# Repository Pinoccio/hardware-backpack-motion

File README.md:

motino-hardware-reference
===========================

Contained are the schematics, board layout, data sheets, and BOM for the Pinoccio motion shield, containing GPS, accelerometer, digital compass, and 3-axis gyro.

The board revisions are also marked as tags in the git repository, if you'd like to see a previous version.

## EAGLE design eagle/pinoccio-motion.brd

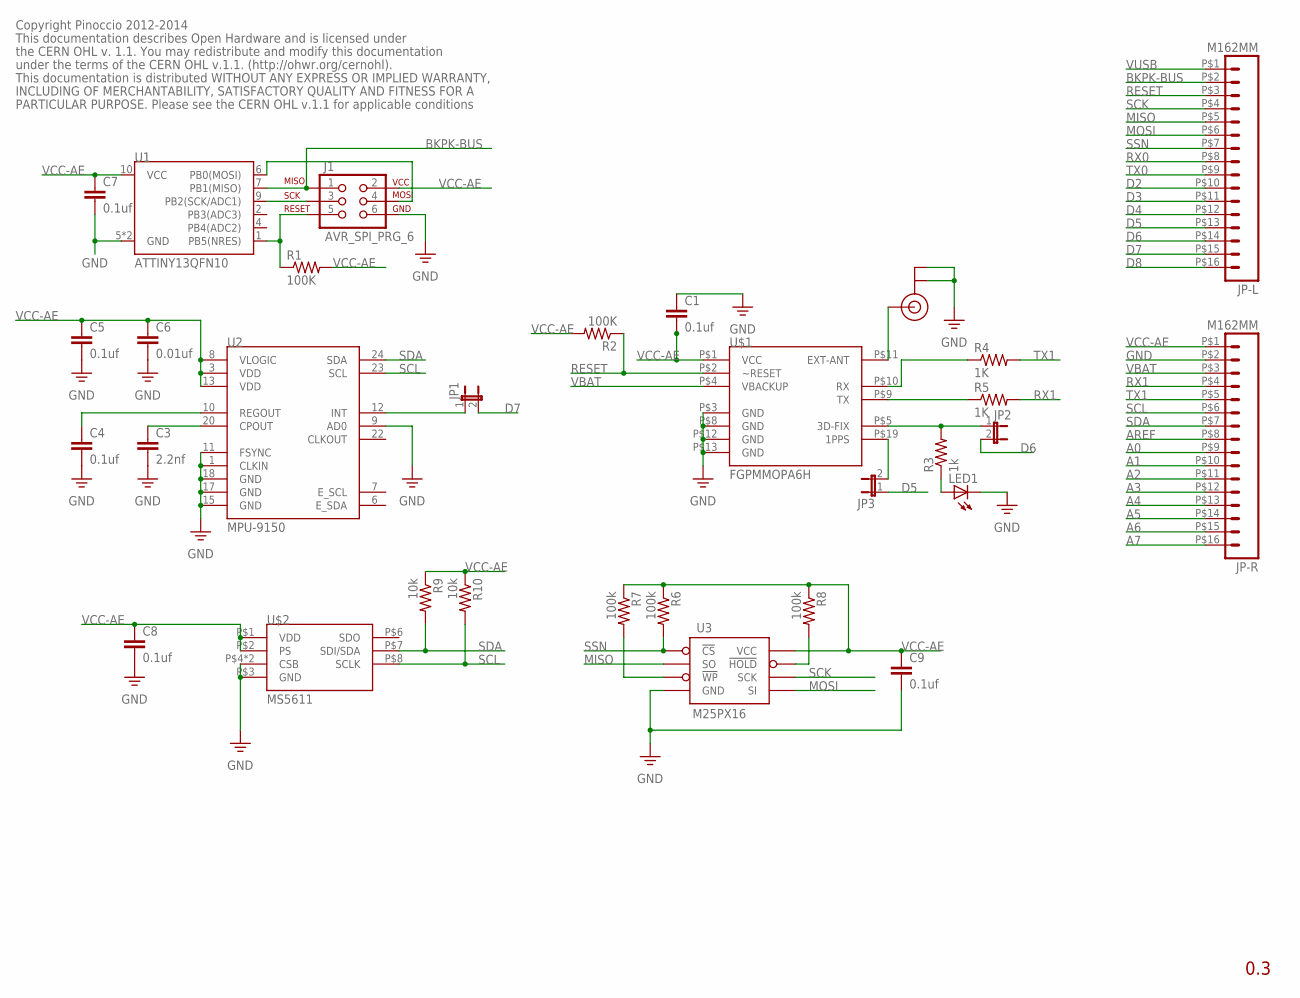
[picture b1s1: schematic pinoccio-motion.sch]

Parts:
C1, C4, C5, C7, C8, C9: 0.1uf; 0402-CAP
C3: 2.2nf; 0603-CAP
C6: 0.01uf; 0402-CAP
J1: AVR_SPI_PRG_6; 2X3-PAD
JP1, JP2, JP3: JUMPER-2SMD-NC; SJ_2S
JP-L: M162MM; 1X16_2MM
JP-R: M162MM; 1X16_2MM
LED1: LED0603; LED-0603
R1, R2: 100K; 0402-RES
R3: 1k; 0402-RES
R4, R5: 1K; 0402-RES
R6, R7, R8: 100k; 0402-RES
R9, R10: 10k; 0402-RES
U1: ATTINY13QFN10; QFN-10
U2: MPU-9150; QFN-24-NP
U3: M25PX16; SO8N
U$1: FGPMMOPA6H
U$2: MS5611
U$4: U.FL

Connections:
A0: JP-R.P$9 (9)
A1: JP-R.P$10 (10)
A2: JP-R.P$11 (11)
A3: JP-R.P$12 (12)
A4: JP-R.P$13 (13)
A5: JP-R.P$14 (14)
A6: JP-R.P$15 (15)
A7: JP-R.P$16 (16)
AREF: JP-R.P$8 (8)
BKPK-BUS: J1.1, JP-L.P$2 (2), U1.7 (PB1(MISO))
D2: JP-L.P$10 (10)
D3: JP-L.P$11 (11)
D4: JP-L.P$12 (12)
D5: JP3.1, JP-L.P$13 (13)
D6: JP2.2, JP-L.P$14 (14)
D7: JP1.2, JP-L.P$15 (15)
D8: JP-L.P$16 (16)
GND: C1.1, C3.2, C4.2, C5.2, C6.2, C7.2, C8.2, C9.2, J1.6, JP-R.P$2 (2), LED1.C, U1.5 (GND), U1.EP (GND), U2.1 (CLKIN), U2.9 (AD0), U2.11 (FSYNC), U2.15 (GND), U2.17 (GND), U2.18 (GND), U3.4 (GND), U$1.P$3 (GND), U$1.P$8 (GND), U$1.P$12 (GND), U$1.P$13 (GND), U$2.P$3 (GND), U$2.P$4 (CSB), U$2.P$5 (CSB), U$4.P$1 (GND), U$4.P$2 (GND)
MISO: JP-L.P$5 (5), U3.2 (SO)
MOSI: JP-L.P$6 (6), U3.5 (SI)
unnamed: J1.4, U1.6 (PB0(MOSI))
unnamed: R4.1, U$1.P$10 (RX)
unnamed: J1.3, U1.9 (PB2(SCK/ADC1))
unnamed: J1.5, R1.1, U1.1 (PB5(NRES))
unnamed: U$1.P$11 (EXT-ANT), U$4.P$3 (SIGNAL)
unnamed: R5.1, U$1.P$9 (TX)
unnamed: JP1.1, U2.12 (INT)
unnamed: C3.1, U2.20 (CPOUT)
unnamed: JP2.1, R3.2, U$1.P$5 (3D-FIX)
unnamed: JP3.2, U$1.P$19 (1PPS)
unnamed: C4.1, U2.10 (REGOUT)
unnamed: R7.2, U3.3 (!WP)
unnamed: R8.2, U3.7 (!HOLD)
unnamed: LED1.A, R3.1
RESET: JP-L.P$3 (3), R2.1, U$1.P$2 (~RESET)
RX0: JP-L.P$8 (8)
RX1: JP-R.P$4 (4), R5.2
SCK: JP-L.P$4 (4), U3.6 (SCK)
SCL: JP-R.P$6 (6), R10.2, U2.23 (SCL), U$2.P$8 (SCLK)
SDA: JP-R.P$7 (7), R9.2, U2.24 (SDA), U$2.P$7 (SDI/SDA)
SSN: JP-L.P$7 (7), R6.2, U3.1 (!CS)
TX0: JP-L.P$9 (9)
TX1: JP-R.P$5 (5), R4.2
VBAT: JP-R.P$3 (3), U$1.P$4 (VBACKUP)
VCC-AE: C1.2, C5.1, C6.1, C7.1, C8.1, C9.1, J1.2, JP-R.P$1 (1), R1.2, R2.2, R6.1, R7.1, R8.1, R9.1, R10.1, U1.10 (VCC), U2.3 (VDD), U2.8 (VLOGIC), U2.13 (VDD), U3.8 (VCC), U$1.P$1 (VCC), U$2.P$1 (VDD), U$2.P$2 (PS)
VUSB: JP-L.P$1 (1)

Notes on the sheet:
0.3
Copyright Pinoccio 2012-2014
This documentation describes Open Hardware and is licensed under
the CERN OHL v. 1.1. You may redistribute and modify this documentation
under the terms of the CERN OHL v.1.1. (http://ohwr.org/cernohl).
This documentation is distributed WITHOUT ANY EXPRESS OR IMPLIED WARRANTY,
INCLUDING OF MERCHANTABILITY, SATISFACTORY QUALITY AND FITNESS FOR A
PARTICULAR PURPOSE. Please see the CERN OHL v.1.1 for applicable conditions

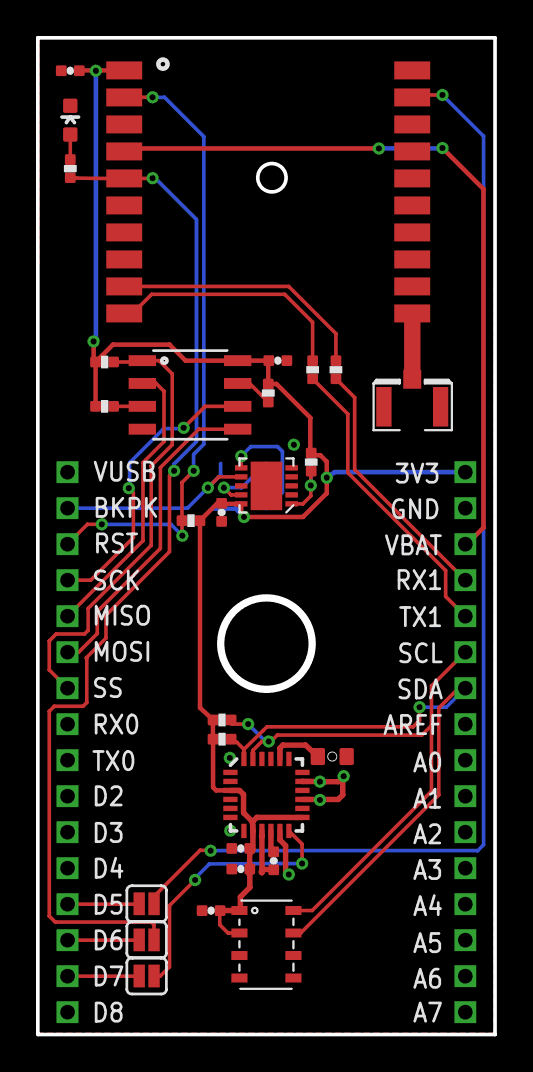
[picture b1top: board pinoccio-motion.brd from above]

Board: 2 copper layers, 25.4 x 55.4 mm, 31 parts (1 on the bottom side), 30 nets.

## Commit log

2013-09-27 updated motion to v0.1
2015-04-07 v0.2 fixes

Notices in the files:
eagle/pinoccio-motion.brd:
Licensed under CERN OHL v.1.1
